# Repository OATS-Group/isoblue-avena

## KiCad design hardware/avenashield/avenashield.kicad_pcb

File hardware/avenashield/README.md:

# ISOBlue-AvenaShield for the Lattepanda Alpha/Delta.

The AvenaShield is an expansion board designed to give the Lattepanda CAN and
LTE connectivity to be used as an IoT device on ag machines. This board includes
two CAN ports, based on the open source hardware board _CANtact_, and a MiniPCI Express 
port to connect LTE modems.

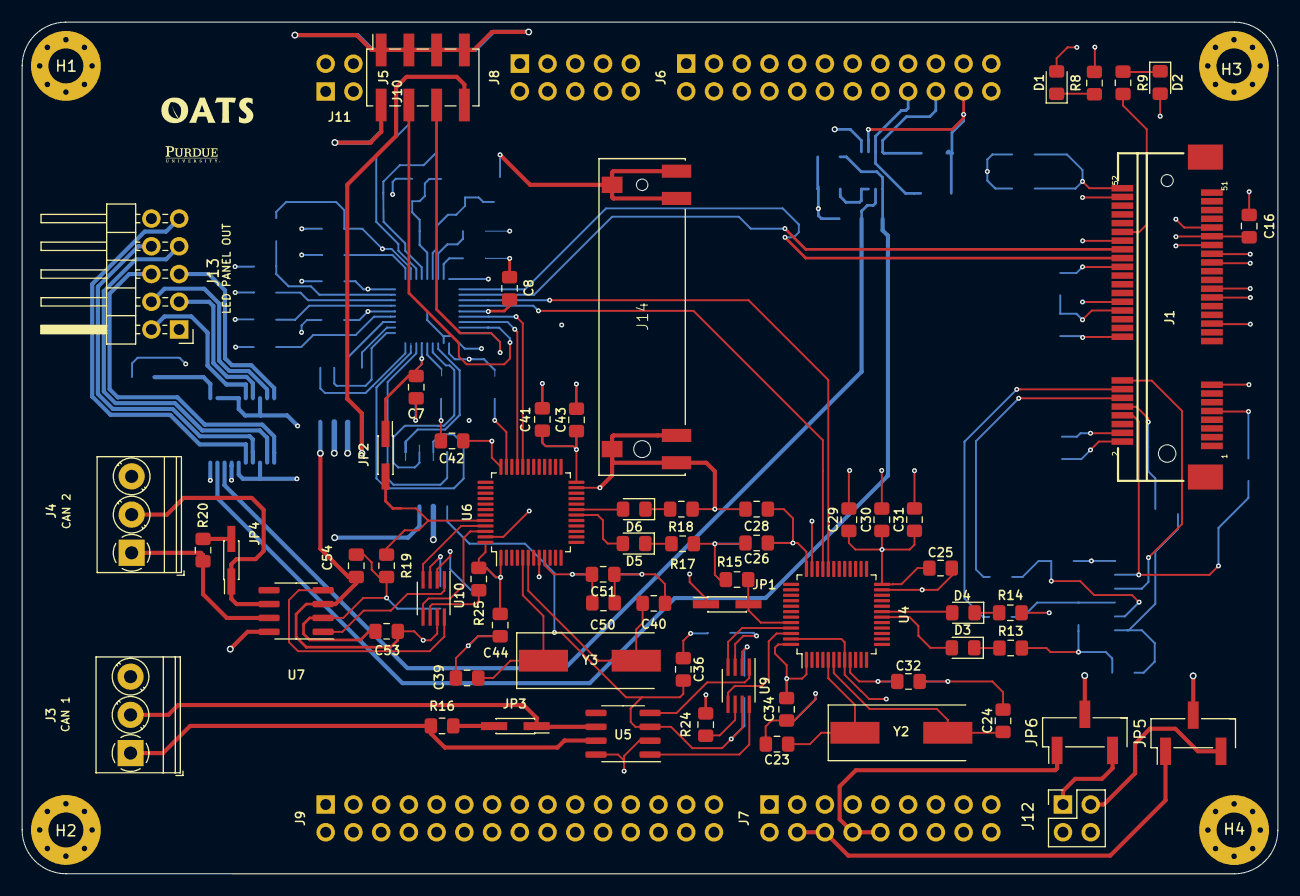
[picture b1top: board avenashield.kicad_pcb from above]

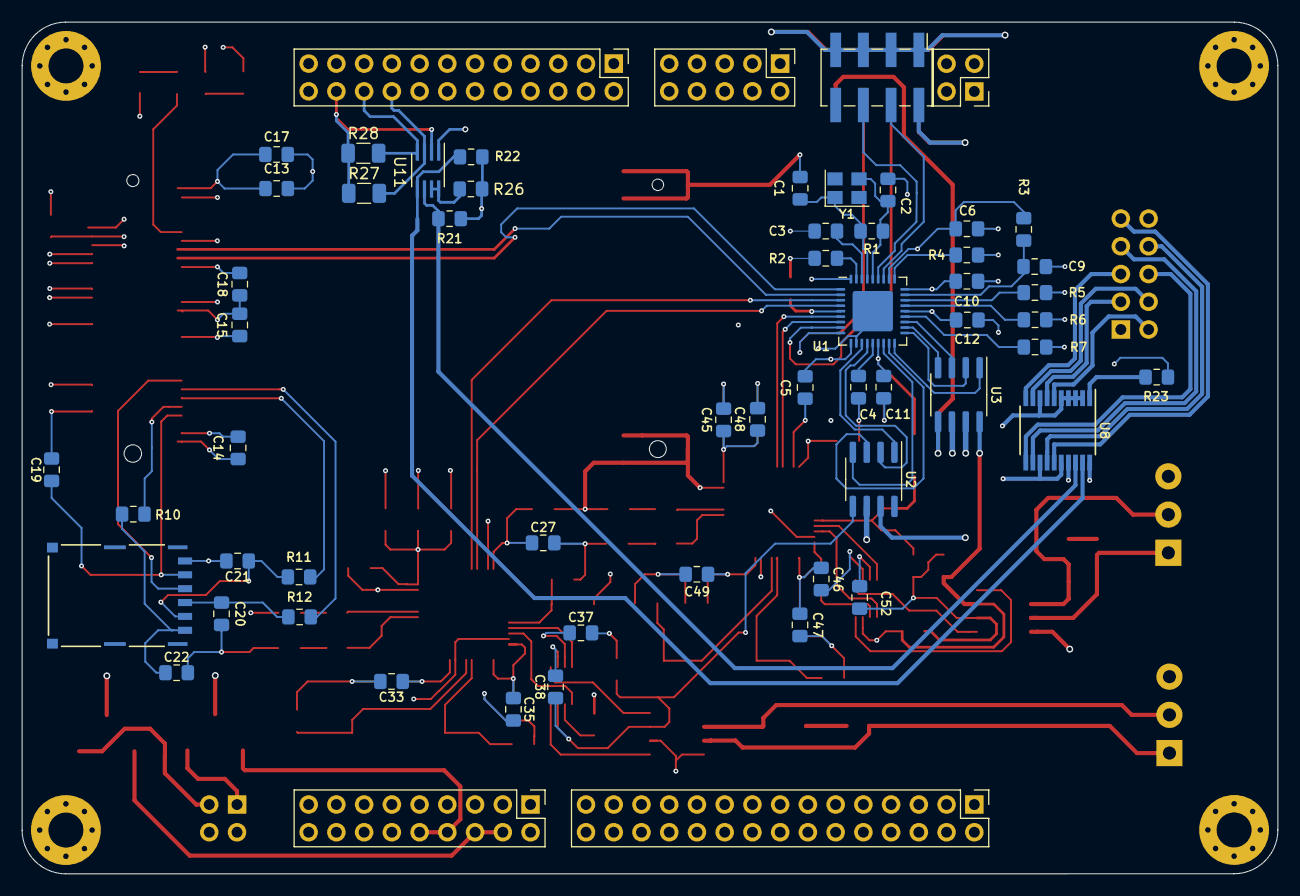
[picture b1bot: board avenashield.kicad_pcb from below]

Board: 4 copper layers, 115.0 x 78.0 mm, 126 parts (59 on the bottom side), 94 nets.

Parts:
C1, C2: 18pF; C_0805_2012Metric_Pad1.15x1.40mm_HandSolder
C3, C4, C5, C6, C7, C8, C9, C10, C11: 0.1uF; C_0805_2012Metric_Pad1.15x1.40mm_HandSolder
C12: 4.7uF; C_0805_2012Metric_Pad1.15x1.40mm_HandSolder
C13, C14, C16, C17: 100u; C_0805_2012Metric_Pad1.15x1.40mm_HandSolder
C15, C18, C19: 100n; C_0805_2012Metric_Pad1.15x1.40mm_HandSolder
C20, C21, C22: 33p; C_0805_2012Metric_Pad1.15x1.40mm_HandSolder
C23, C24, C39, C40: 18p; C_0805_2012Metric_Pad1.15x1.40mm_HandSolder
C25, C26, C27, C29, C30, C34, C36, C37, C38, C41, C42, C43, C45, C46, C50, C52, C53, C54: 0.1u; C_0805_2012Metric_Pad1.15x1.40mm_HandSolder
C28, C31, C35, C44, C47, C51: 4.7u; C_0805_2012Metric_Pad1.15x1.40mm_HandSolder
C32, C48: 10n; C_0805_2012Metric_Pad1.15x1.40mm_HandSolder
C33, C49: 1u; C_0805_2012Metric_Pad1.15x1.40mm_HandSolder
D1: MODEM_PWR; LED_0805_2012Metric_Pad1.15x1.40mm_HandSolder
D2: WWAN; LED_0805_2012Metric_Pad1.15x1.40mm_HandSolder
D3, D4, D5, D6: LED; LED_0805_2012Metric_Pad1.15x1.40mm_HandSolder
H1: MOUNT_PAD1; MountingHole_3.2mm_M3_Pad_Via
H2: MOUNT_PAD2; MountingHole_3.2mm_M3_Pad_Via
H3: MOUNT_PAD3; MountingHole_3.2mm_M3_Pad_Via
H4: MOUNT_PAD4; MountingHole_3.2mm_M3_Pad_Via
J1: Bus_PCI_Express_Mini; TE_1775862-2
J2: SIM_Card; CONN-693043020611
J3: CAN_TRA_HEADER; TerminalBlock_Phoenix_PT-1,5-3-3.5-H_1x03_P3.50mm_Horizontal
J4: CAN_IMP_HEADER; TerminalBlock_Phoenix_PT-1,5-3-3.5-H_1x03_P3.50mm_Horizontal
J5: USB Headers Board Top; PinSocket_2x04_P2.54mm_Vertical_SMD
J6: Lattepanda Upper Left Header (I2C and I2S); PinHeader_2x12_P2.54mm_Vertical
J7: Lattepanda Upper Right Header (BIOS SPI); PinHeader_2x09_P2.54mm_Vertical
J8: Lattepanda Middle Left Header (RS-232); PinHeader_2x05_P2.54mm_Vertical
J9: Lattepanda Lower Right Header (Arduino Pins); PinHeader_2x15_P2.54mm_Vertical
J10: Lattepanda Lower Left Header (USB); PinHeader_2x04_P2.54mm_Vertical_SMD
J11: 12V DC IN Headers; PinHeader_2x02_P2.54mm_Vertical
J12: EXT PWR IN; PinHeader_2x02_P2.54mm_Vertical
J13: LED_OUT; PinHeader_2x05_P2.54mm_Horizontal
J14: JAE_MM60-EZH059-B5-R650
JP1, JP2: Boot Mode; PinHeader_2x01_P1.27mm_Vertical_SMD
JP3: Termination Enable; PinHeader_2x01_P1.27mm_Vertical_SMD
JP4: Termination enable; PinHeader_2x01_P1.27mm_Vertical_SMD
JP5: 3.3V SRC SEL; PinHeader_1x03_P2.54mm_Vertical_SMD_Pin1Left
JP6: 5V SRC SEL; PinHeader_1x03_P2.54mm_Vertical_SMD_Pin1Left
R1: 1M; R_0805_2012Metric_Pad1.15x1.40mm_HandSolder
R2: 12k; R_0805_2012Metric_Pad1.15x1.40mm_HandSolder
R3, R4, R5, R6, R7: 100k; R_0805_2012Metric_Pad1.15x1.40mm_HandSolder
R8, R9: 330; R_0805_2012Metric_Pad1.15x1.40mm_HandSolder
R10, R11, R12: 47; R_0805_2012Metric_Pad1.15x1.40mm_HandSolder
R13, R14, R16, R17, R18, R20: 120; R_0805_2012Metric_Pad1.15x1.40mm_HandSolder
R15, R19: 510; R_0805_2012Metric_Pad1.15x1.40mm_HandSolder
R21, R22, R23: 4.7k; R_0805_2012Metric_Pad1.15x1.40mm_HandSolder
R24, R25: 10k; R_0805_2012Metric_Pad1.15x1.40mm_HandSolder
R26: 200k; R_0805_2012Metric_Pad1.15x1.40mm_HandSolder
R27, R28: 4.7k; R_1206_3216Metric
U1: USB2514B_Bi; QFN-36-1EP_6x6mm_P0.5mm_EP3.7x3.7mm
U2, U3: MIC2026-1BM; SOIC-8_3.9x4.9mm_P1.27mm
U4, U6: STM32F042C6Tx; LQFP-48_7x7mm_P0.5mm
U5, U7: MCP2551-I-SN; SOIC-8_3.9x4.9mm_P1.27mm
U8: TLC59108xPW; TSSOP-20_4.4x6.5mm_P0.65mm
U9, U10: TXS0102DCT; SSOP-8_2.95x2.8mm_P0.65mm
U11: PCA9306; SSOP-8_2.95x2.8mm_P0.65mm
Y1: 24 MHz; Crystal_SMD_3225-4Pin_3.2x2.5mm
Y2, Y3: 16 MHz; Crystal_SMD_HC49-SD

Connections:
+3V3: C5.1, C6.1, C7.1, C8.1, C10.1, C11.1, C12.1, C13.1, C14.1, C15.1, C16.1, C17.1, C18.1, C25.1, C26.1, C27.1, C28.1, C29.1, C30.1, C31.1, C32.1, C33.1, C34.1, C35.1, C37.1, C41.1, C42.1, C43.1, C44.1, C45.1, C46.1, C47.1, C48.1, C49.1, C50.1, C51.1, C52.1, D1.2, J1.2, J1.24, J1.39, J1.41, J1.52, JP1.1, JP2.1, JP5.1, R3.1, R24.2, R25.1, U1.5, U1.10, U1.15, U1.23, U1.27, U1.29, U1.36, U4.1, U4.9, U4.24, U4.36, U4.48, U6.1, U6.9, U6.24, U6.36, U6.48, U9.3, U10.3
+5V: J13.1, JP6.1, R21.1, R22.1, R26.1, U2.7, U3.7, U8.17, U8.20
/Lattepanda/BOARD_1V8: J6.22, R27.1, R28.1, U11.2
/Lattepanda/BOARD_SCL: J6.18, R27.2, U11.3
/Lattepanda/BOARD_SDA: J6.20, R28.2, U11.4
/Lattepanda/EXT_3V3: J12.2, JP5.2
/Lattepanda/EXT_5V: J12.1, JP6.2
/Lattepanda/USB_DM: J10.4, U1.30
/Lattepanda/USB_DP: J10.6, U1.31
/MiniPCIe2USB.sch/USB_DM: J1.36, U1.1
/MiniPCIe2USB.sch/USB_DP: J1.38, U1.2
/USB2CAN_IMP/BOARD_5V: C53.1, C54.2, U3.8, U7.3, U10.7
/USB2CAN_IMP/CAN_H: J4.1, R20.1, U7.7
/USB2CAN_IMP/CAN_L: J4.2, JP4.1, U7.6
/USB2CAN_IMP/USB_DM: U1.6, U6.32
/USB2CAN_IMP/USB_DP: U1.7, U6.33
/USB2CAN_TRA/BOARD_5V: C36.2, C38.1, U2.5, U5.3, U9.7
/USB2CAN_TRA/CAN_H: J3.1, R16.1, U5.7
/USB2CAN_TRA/CAN_L: J3.2, JP3.1, U5.6
/USB2CAN_TRA/USB_DM: U1.3, U4.32
/USB2CAN_TRA/USB_DP: U1.4, U4.33
/USB_HEADERS/BOARD_5V: J5.8, U3.5
/USB_HEADERS/USB_DM: J5.4, U1.8
/USB_HEADERS/USB_DP: J5.6, U1.9
GNDREF: C1.2, C2.2, C3.2, C4.2, C5.2, C6.2, C7.2, C8.2, C9.2, C10.2, C11.2, C12.2, C13.2, C14.2, C15.2, C16.2, C17.2, C18.2, C19.2, C20.2, C21.2, C22.2, C23.2, C24.2, C25.2, C26.2, C27.2, C28.2, C29.2, C30.2, C31.2, C32.2, C33.2, C34.2, C35.2, C36.1, C37.2, C38.2, C39.2, C40.2, C41.2, C42.2, C43.2, C44.2, C45.2, C46.2, C47.2, C48.2, C49.2, C50.2, C51.2, C52.2, C53.2, C54.1, D2.2, H1.1, H2.1, H3.1, H4.1, J1.4, J1.9, J1.15, J1.18, J1.21, J1.26, J1.27, J1.29, J1.34, J1.35, J1.37, J1.40, J1.43, J1.50, J2.5, J3.3, J4.3, J5.1, J5.2, J5.3, J5.5, J5.7, J6.1, J6.17, J6.19, J6.21, J6.23, J10.1, J10.2, J10.3, J10.5, J10.7, J12.3, J12.4, J13.10, J14.S1_1, J14.S1_2, J14.S1_3, J14.S2_1, J14.S2_2, J14.S2_3, R2.2, R4.2, R5.2, R6.2, R7.2, R8.2, R13.2, R14.2, R15.2, R17.2, R18.2, R19.2, R23.2, U1.11, U1.37, U2.6, U3.6, U4.8, U4.23, U4.35, U4.47, U5.2, U5.8, U6.8, U6.23, U6.35, U6.47, U7.2, U7.8, U8.2, U8.3, U8.4, U8.5, U8.8, U8.13, U8.16, U9.2, U10.2, U11.1
unnamed: C1.1, R1.1, U1.33, Y1.1
unnamed: C2.1, R1.2, U1.32, Y1.2
unnamed: C3.1, U1.34
unnamed: C4.1, U1.14
unnamed: C9.1, R3.2, U1.26
unnamed: C19.1, J1.8, J2.1
unnamed: C20.1, J2.2, R12.1
unnamed: C21.1, J2.3, R11.1
unnamed: C22.1, J2.7, R10.1
unnamed: C23.1, U4.5, Y2.1
unnamed: C24.1, U4.6, Y2.2
unnamed: C39.1, U6.5, Y3.1
unnamed: C40.1, U6.6, Y3.2
unnamed: D1.1, R8.1
unnamed: D2.1, R9.1
unnamed: D3.1, R13.1
unnamed: D3.2, U4.18
unnamed: D4.1, R14.1
unnamed: D4.2, U4.19
unnamed: D5.1, R17.1
unnamed: D5.2, U6.18
unnamed: D6.1, R18.1
unnamed: D6.2, U6.19
unnamed: J1.10, R10.2
unnamed: J1.12, R11.2
unnamed: J1.14, R12.2
unnamed: J1.16, J2.6
unnamed: J1.42, R9.2
unnamed: J7.4, J7.6, JP5.3
unnamed: J7.8, J7.10, JP6.3
unnamed: J13.2, U8.6
unnamed: J13.3, U8.7
unnamed: J13.4, U8.9
unnamed: J13.5, U8.10
unnamed: J13.6, U8.11
unnamed: J13.7, U8.12
unnamed: J13.8, U8.14
unnamed: J13.9, U8.15
unnamed: JP1.2, R15.1, U4.44
unnamed: JP2.2, R19.1, U6.44
unnamed: JP3.2, R16.2
unnamed: JP4.2, R20.2
unnamed: R2.1, U1.35
unnamed: R4.1, U1.28
unnamed: R5.1, U1.25
unnamed: R6.1, U1.24
unnamed: R7.1, U1.22
unnamed: R21.2, U8.18, U11.6
unnamed: R22.2, U8.19, U11.5
unnamed: R23.1, U8.1
unnamed: R24.1, U9.6
unnamed: R25.2, U10.6
unnamed: R26.2, U11.7, U11.8
unnamed: U1.12, U2.1
unnamed: U1.13, U2.2
unnamed: U1.16, U2.4
unnamed: U1.17, U2.3
unnamed: U1.18, U3.1
unnamed: U1.19, U3.2
unnamed: U1.20, U3.4
unnamed: U1.21, U3.3
unnamed: U4.45, U9.4
unnamed: U4.46, U9.5
unnamed: U5.1, U9.8
unnamed: U5.4, U9.1
unnamed: U7.1, U10.1
unnamed: U6.45, U10.4
unnamed: U6.46, U10.5
unnamed: U7.4, U10.8
